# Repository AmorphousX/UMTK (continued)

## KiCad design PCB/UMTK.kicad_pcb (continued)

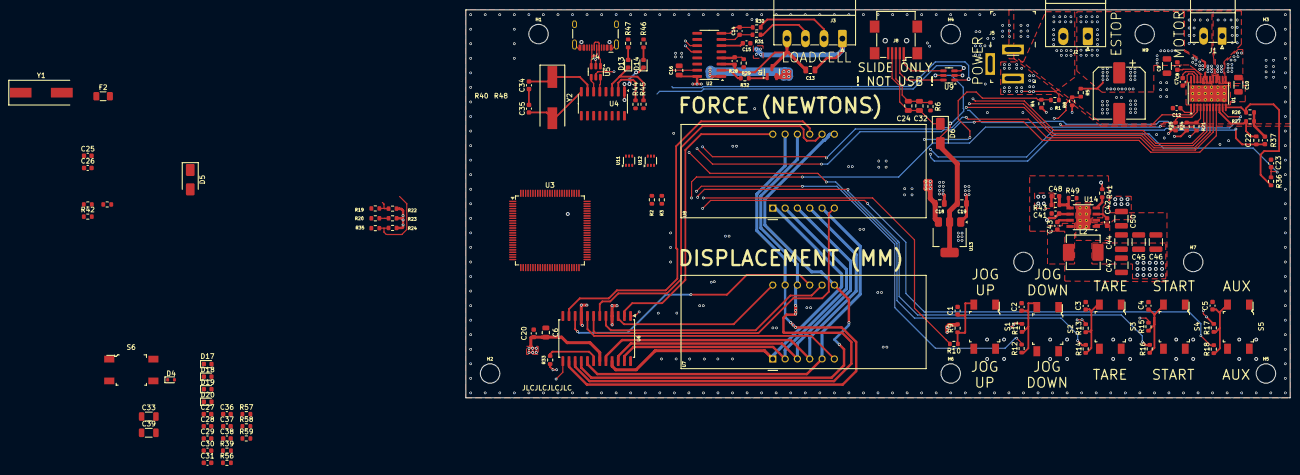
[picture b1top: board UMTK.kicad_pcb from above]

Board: 4 copper layers, 170.0 x 80.0 mm, 146 parts (1 on the bottom side), 114 nets.

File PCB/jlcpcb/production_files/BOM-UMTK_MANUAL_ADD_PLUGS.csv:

Comment,Designator,Footprint,LCSC
1u hv,"C10,C9",C_1206_3216Metric,C13832
0u1,"C1,C14,C15,C2,C20,C22,C23,C3,C4,C5",C_0603_1608Metric,C14663
MBR0560,D1,D_SOD-123,C150515
1u 16v,"C12,C8",C_0603_1608Metric,C15849
10u,"C13,C16,C18,C19,C6",C_0805_2012Metric,C15850
47n,C7,C_0603_1608Metric,C1622
0R,"R25,R32,R6,R7",R_0603_1608Metric,C21189
1K,"R2,R3,R30,R31",R_0603_1608Metric,C21190
DRV8873SPWPRQ1,U1,HTSSOP-24-1EP_4.4x7.8mm_P0.65mm_EP3.4x7.8mm_Mask2.4x4.68mm_ThermalVias,C2150479
100r,"R10,R12,R14,R16,R18",R_0603_1608Metric,C22775
13k,R28,C_0603_1608Metric,C22797
4k7,R29,R_0603_1608Metric,C23162
680R,"R26,R27",R_0603_1608Metric,C23228
LM2576HVS-5,U10,TO-263-5_TabPin3,C234209
100k,"R1,R5",R_0603_1608Metric,C25803
10k,"R11,R13,R15,R17,R22,R23,R33,R35,R36,R37,R4,R8,R9",R_0603_1608Metric,C25804
1000u,C21,CP_Elec_8x10.5,C280406
Header 2x21,HD3,Dummy_Header_2x21,C2883994
Header 2x16,HD4,Dummy_Header_2x16,C2897417
ESTOP,J2,"PhoenixContact_MSTBA_2,5_2-G-5,08_1x02_P5.08mm_Horizontal",C3697
100u,L1,L_Sunlord_MWSA1206S-101,C408533
TLV76133DCY,U13,SOT-223-3_TabPin2,C435835
Header 2x3,"HD1,HD2",Dummy_Header_2x3,C5116527
FSM4JSMATR,"S1,S2,S3,S4,S5",Switch_Tactile_SMD_6x6mm,C5127964
PJ-102BH,J5,Barrel_Jack_5.5mmODx2.1mmID_PJ-202A,C5353839
100u hv,"C11,C17",CP_Elec_10x10.5,C5355007
CA56-12EWA,"U7,U8",CA56-12EWA,C54396
HX711,U2,SOP-16_3.9x9.9mm_P1.27mm,C6705483
ZENER 5V,"D2,D3",D_SOD-523,C72244
LOADCELL,J3,"PhoenixContact_MC_1,5_4-G-3.81_1x04_P3.81mm_Horizontal",C7245
Q_PNP_BEC,Q1,SOT-23,C8542
Motor Out,J1,"PhoenixContact_MC_1,5_2-G-3.81_1x02_P3.81mm_Horizontal",C880581
10033526-N3212LF,J8,USB_Mini-B_Wuerth_65100516121_Horizontal,C91144
SN74LVC1T45DCK,"U11,U12",SOT-363_SC-70-6,C9382
MAX7221xWG,U6,SOIC-24W_7.5x15.4mm_P1.27mm,C9964
MotorOutPlug,P1,Plug for J1,C8466
EstopPlug,P2,Plug for J2,C71370
LoadcellPlug,P3,Plug for J3,C7244

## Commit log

2022-09-18 Initial Commit, Arduino Code
    Copy in arduino code from long ago
2022-09-18 previous umtk arduino code
2022-09-18 New UI folder added, reference code from MMTK uploaded
2022-09-19 Convert to platformio, and working
    Converted project to use platformIO, better than arduino IDE.
    Also updated arduino code now it works with MMTK UI for display, tear, start, and stop
2022-09-21 Directory clean up
2022-09-21 CHANGE FOLDER NAME
2022-10-05 Hoist function definitions, change states
    Hoisted function definitions to start of file of compiler knows about it at link time.
    Updated UMTK states to match numbers for MMTK so a unmodified MMTK UI have sensible state numbers
2022-10-05 Platform IO meta
    Push some platform io metadata
2022-10-05 Clean up old pio folder
2024-06-25 Initial of UMTK_V1
2024-06-25 Import Schematic from altium
2024-06-27 Put in Files for V1
2024-06-27 Updated Schematics
    Done: 7 Seg, Power, Motor, Slide, HX711
    To Do: Arduino
2024-06-27 Export Subsheet Pin From 7Seg
2024-06-27 Prettfy
2024-06-28 Updating Schematic
2024-06-30 Schematic Done, Assigning footprint
2024-06-30 Footprint assign
2024-06-30 ERC good, imported into PCB
2024-06-30 Updated DRC and pcb
2024-06-30 Initial Place, Board Stack
2024-06-30 Layout Started
2024-07-01 Layout Continue
2024-07-02 Placement Approved, Added holes
2024-07-02 Routing
2024-07-03 WIP laying board
2024-07-06 Dumbass has push and shove routing off
2024-07-06 Routing Done
2024-07-06 Added Sinkscreen Annotations, PCB Done for now
2024-07-06 Generating outputs
2024-07-07 Assigning JLC
2024-07-08 Routing and JLC Assignment Done
2024-07-08 PCB improvment
2024-07-09 Seem to be all done
2024-07-09 Grounding Improvments
2024-07-09 improve vias location
2024-07-11 Generate step file, board looks good submitting
2024-07-11 Uodated Production File, added JLC part number
2024-07-12 Update PCB and production files, production files sent
2024-07-27 Bug fixes and add dummy headers for DFM
    Fix:
    - Power jack footprint incorrect for high current jack
    - Motor and Estop terminal hole size too small
    - Added designator and position for arduino headers for DFM
2024-07-27 Added pin assignment doc for firmware
2024-07-28 Make simple components bigger
2024-07-28 Firmware Dev, Added Lib for MAX7219
2024-07-29 Debugging firmware, feature add
    Added feature to disable leading zeros and turn them off.
    Updating PCB, all general parts should be 0603 by default.
    Add configratble decimal point location
2024-07-31 Updated slide pinout, add protection, Fixed some issues
2024-07-31 Add a bit of decoupling for 7seg driver
2024-07-31 Add devoupling for 7seg
2024-08-01 Move interrupr pin to 3, Move motor sleep to 14 so 13 can LED
2024-08-01 Update pin map, remove one from PCB files
2024-08-01 Cleanup and update PCB
2024-08-02 Slide Debugged
2024-08-02 Update Firmware
2024-08-03 PCB Revision
    - Add filter for 7seg power again
    - Add low pass filter for output of motor power sense
2024-08-03 JLC Assigned for updated PCB, ready to send again
2024-08-03 Update DRC
2024-08-03 Convert Project to PlatformIO
2024-08-03 Add job by serial
2024-08-04 Jog by serial done, should tweak the jog timer
2024-08-04 Add Firmware API Docs
2024-08-04 Added new gui to git, add voltages to firmware prints
2024-08-04 Make Jog from GUI work
2024-08-04 Slow down GUI, it gets bogged down a lot at fast rates
2024-08-04 Add simple filtering to loadcell reading, slow PID loop
2024-08-04 Updated speed setter a bit, it's not that great yet
2024-08-04 UPdate PCB for better thermals for motor driver
2024-08-04 Update PCB, Generate JLC again
2024-08-04 Update PCB Back Silkscreen
2024-08-04 Update stuff, jlc seems broken for some reason
2024-08-05 Update prod File Remove old silkscreen notes from front
2024-08-05 Sent Production Batch 2 for 1.5
2024-08-06 Update UMTK_UI_1v5.py
    Re modified the UI.
    - Removed dial, and duplicate buttons
    - Added text field to set speed.
2024-08-09 Updated prod file to include plug side connectors
2024-08-17 Added Calibration menu
    new layout, calibration labels, inline text box and labels
2024-08-17 Update Arduino Code for V1.5 Run of PCB
2024-08-17 WIP Save buttons and plot working
2024-08-17 Motor bars work but I don't like how it looks rn
2024-08-18 Add direction ability
2024-08-18 Restore calibration from eeprom, Add a calibration rescue
2024-08-18 Make button inputs pullup so buttons read as high when not connected
2024-08-18 Start to refactor code to make it more readable
2024-08-18 Seperate serial functions into own file. Improve tare handling in firmware
2024-09-06 Update motor sense voltage reading
2024-09-08 UI Updates - change motor stall progress bar to button
    UI Updates - change motor stall progress bar to button
2024-09-08 qt design file
    qt design file
2024-09-08 .ui file update
2024-09-08 Update with conflicts
2024-09-08 .ui file updates
2024-09-08 ui changes
2024-09-08 resizing ui
2024-09-08 added cat
2024-09-08 Add img folder, sync changes
2024-09-08 cat image folder
2024-09-09 Remove motor stall detection from firmware, add it in GUI only
2024-09-09 Add theme
2024-09-09 Add a cat for both dark and light, cat alignment
2024-09-10 Estop and serial connect updates to main.py
2024-09-12 update firmware, current sens pins flipped, update header text to be correct
2024-09-13 removed entrypoint and cache
2024-09-14 macos-zip
2024-09-15 Clean up arduino folders and move files
2024-09-15 Add stall detection and stop functionality
2024-09-15 umtk zip windows os
2024-09-15 added logging to main.py
2024-09-15 Add QA checklist, update firmware to reset caliration properly
2024-09-16 Firmware fixes to correctly store data for calibration
2024-09-16 remove pycache, add comatibility for gui logging millis
2024-09-16 Gui function update, fix motor stall button red, validate against new firmware
2024-09-16 Update gui make window smaller
2024-09-16 make graph right sizez
2024-09-16 updated gui design screen smallers
2024-09-16 Fix emergency stop display
2024-09-17 update gui, estop volts threashold is 8v now
2024-09-19 updated macos zip
2024-09-21 windows ui zip update
2024-09-21 move v1 to old
2024-09-21 Clean up windows zip to remove macos file and pycache
2024-09-21 revert last change
2024-09-21 minor change in the way date time format is saved
2024-09-21 update windows files properly
2024-09-21 Clean windows zip again
2024-09-21 pushing windows and macos scripts
2024-09-22 Add package script
2024-09-22 add packaging script
2024-11-02 Remove files from v1 and v1.5
2024-11-03 Update PCB to seperate ground symbols apporiately. Modify board to sepearte ground path for motor current and all other devices. Add filtering for slide power, hopefully reduce bownout or other issue.
2024-11-07 Starting work to put arduino chip directly onboard
2025-03-30 WIP Adding adudino onboard, so far copying pro mega
2025-04-06 Schematic bit done for adding arduino, improved motor maybe a bit by adding caps, improved slide a bit by adding protection and more caps
2025-04-06 Changed power stage, there as a mistake, also generally changing lots of stuff
2025-04-06 Progress save, schematic done
2025-04-08 Laying out
2025-08-29 Chatgpt make the gui dynamic sizing, so good
2025-08-29 Chatgpt can even do designer ui files, crazy
2025-08-31 remove old gui folders from umtk
2025-08-31 AI Added github workflow to build packages
2025-08-31 Dummy workflow
2025-08-31 Dummy workflow (#4)
2025-09-16 AI fix windows installer
2025-09-16 Make release optional
2025-09-16 Don't need linux tar anymoe github provides source zip
2025-09-16 restore linux tar
2025-09-16 name gui packaging
2025-09-16 make box bigger
2025-09-16 reorg repo a little
2025-09-22 Sync changes AI added stuff
2025-10-01 ir runs now
2025-10-04 add recording widget, and serial port filter to show ch340 only by default
2025-10-05 Update recording wigit, improved unit display
2025-10-05 Imptove gui look, working on fixing force direction for calibration
2025-10-05 INITIAL RELEASE 1.6 GUI
2025-10-06 Layout cleanup, and fix theme issue, make number display better
2025-10-06 Updated installer and package scripts
2025-10-06 Improve mac script maybe
2025-10-06 Install step improvment again
2025-10-06 GH workflow missed files
2025-10-06 remove pyqt6 req
2025-10-06 try to fix import issue
2025-10-06 clean up github action
2025-10-09 don't do onefile
2025-10-09 release files?
2025-10-13 Manually fix macos intel packager
2025-10-13 Test package with spec
2025-10-13 Move UI files up one folder
2025-10-13 Update path in github workflow
2025-10-13 update pyinstaller
2025-10-13 fix pyinstall specing
2025-10-13 package mac on older os, trying to see why fail
2025-10-13 update packager trying to fix macos issue
2025-10-13 update packager trying to fix macos issue, AI is falling down
2025-10-13 mac-package issue
2025-10-13 try folder mode
2025-10-13 trying to fix mac issue
2025-10-13 Path was wrong for mac
2025-10-13 try fix mac
2025-10-13 fix workflow
2025-10-14 fix release files, cleanup name for python package
2025-10-15 Working on mac package, seperate other ones
2025-10-16 Reorg folder structures, AI woke up and started working, try mac package from github now
2025-10-16 Ai bad at yaml
2025-10-16 Fix trivial packageing issue
2025-10-17 Various improvments to graph display size, and button and element scaling, and recording start stop logic
2025-10-17 Clean up mac readme
2025-10-17 Update the mac readme
2025-10-17 add units to axis
2025-10-17 button colors
2025-10-17 ai not smart enough to fix cat picture
2025-10-17 button color fixed for linxu
2025-10-17 fixing theme
2025-10-17 Button color wrong
2025-10-21 Fix big light button
2025-10-21 Fix usb serial detection
2025-10-21 Fix estop not returning
2025-10-22 Add emergency stop text
